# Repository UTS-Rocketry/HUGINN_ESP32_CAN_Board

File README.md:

# CAN Logger

A compact CAN bus logger and sniffer built for the Shingleback rocket. Built around the ESP32-C3 and SN65HVD230 transceiver, it sits on the CAN bus during ground support and pre-launch operations, streaming frames from the flight computer, sensor nodes, CAS board, and camera board over WiFi via MQTT for real-time monitoring.

## Overview

This board is designed for ground support and pre-launch monitoring of the Shingleback CAN bus. It passively sniffs CAN traffic and publishes decoded frames to an MQTT broker over WiFi, making it easy to verify system state, check sensor health, and monitor inter-board communication before launch.

## Hardware

| Component | Part |
|---|---|
| Microcontroller | ESP32-C3 |
| CAN Transceiver | SN65HVD230 |
| Power Input | 3.3V |

## Features

- CAN 2.0A/B frame capture
- Real-time publishing over WiFi via MQTT
- Passive monitoring, no interference with the CAN bus
- Compact form factor suitable for ground support equipment

## Monitored Systems

This board is intended to sniff traffic from the following Shingleback subsystems:

- Flight computer
- CAS board
- Camera board

## Status

Early prototype / bring-up phase. Not recommended for production use.

## License

MIT

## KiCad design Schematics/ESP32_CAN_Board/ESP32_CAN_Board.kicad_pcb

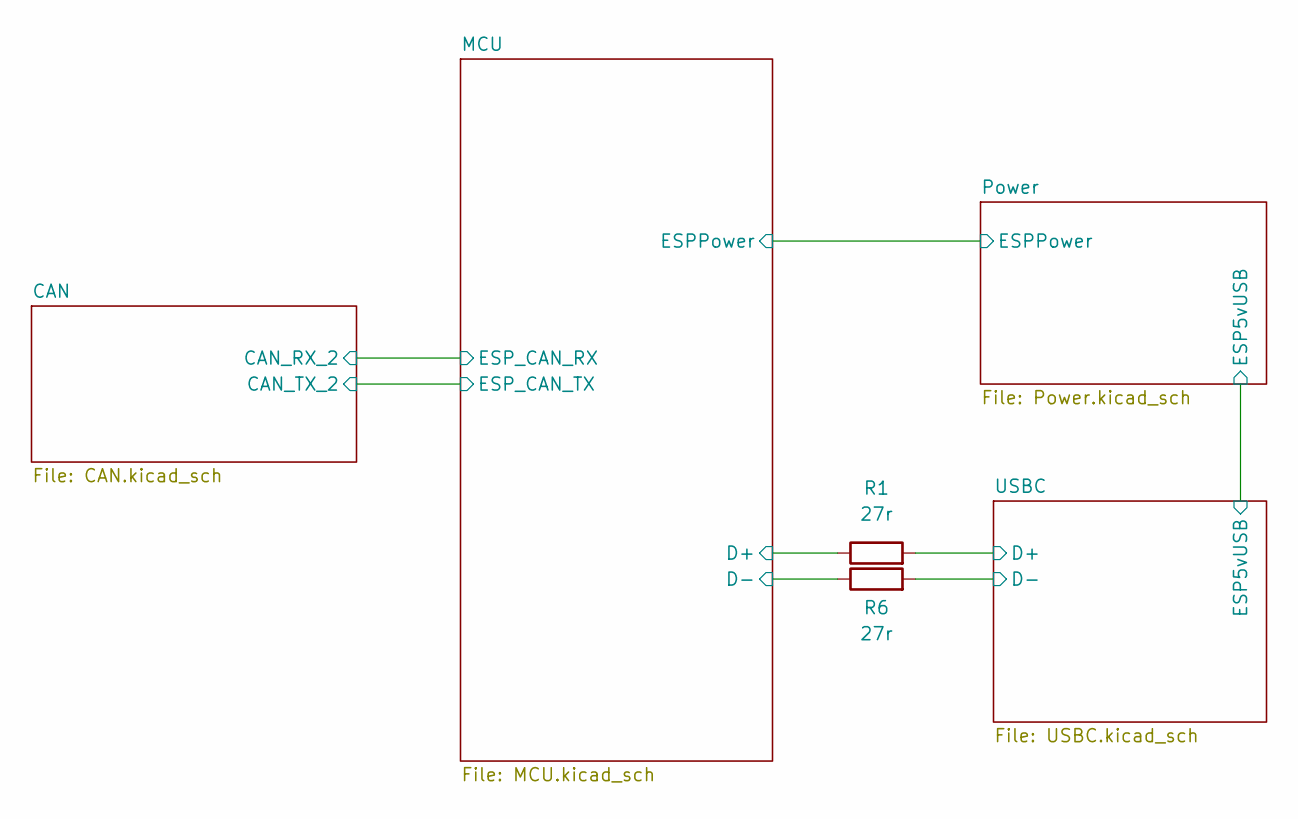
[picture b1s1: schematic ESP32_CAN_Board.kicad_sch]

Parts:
R1, R6: 27r; R_0805_2012Metric_Pad1.20x1.40mm_HandSolder; LCSC C17594

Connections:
/MCU/D+: R1.1; also elsewhere on the board
/MCU/D-: R6.1; also elsewhere on the board
/USBC/D+: R1.2; also elsewhere on the board
/USBC/D-: R6.2; also elsewhere on the board

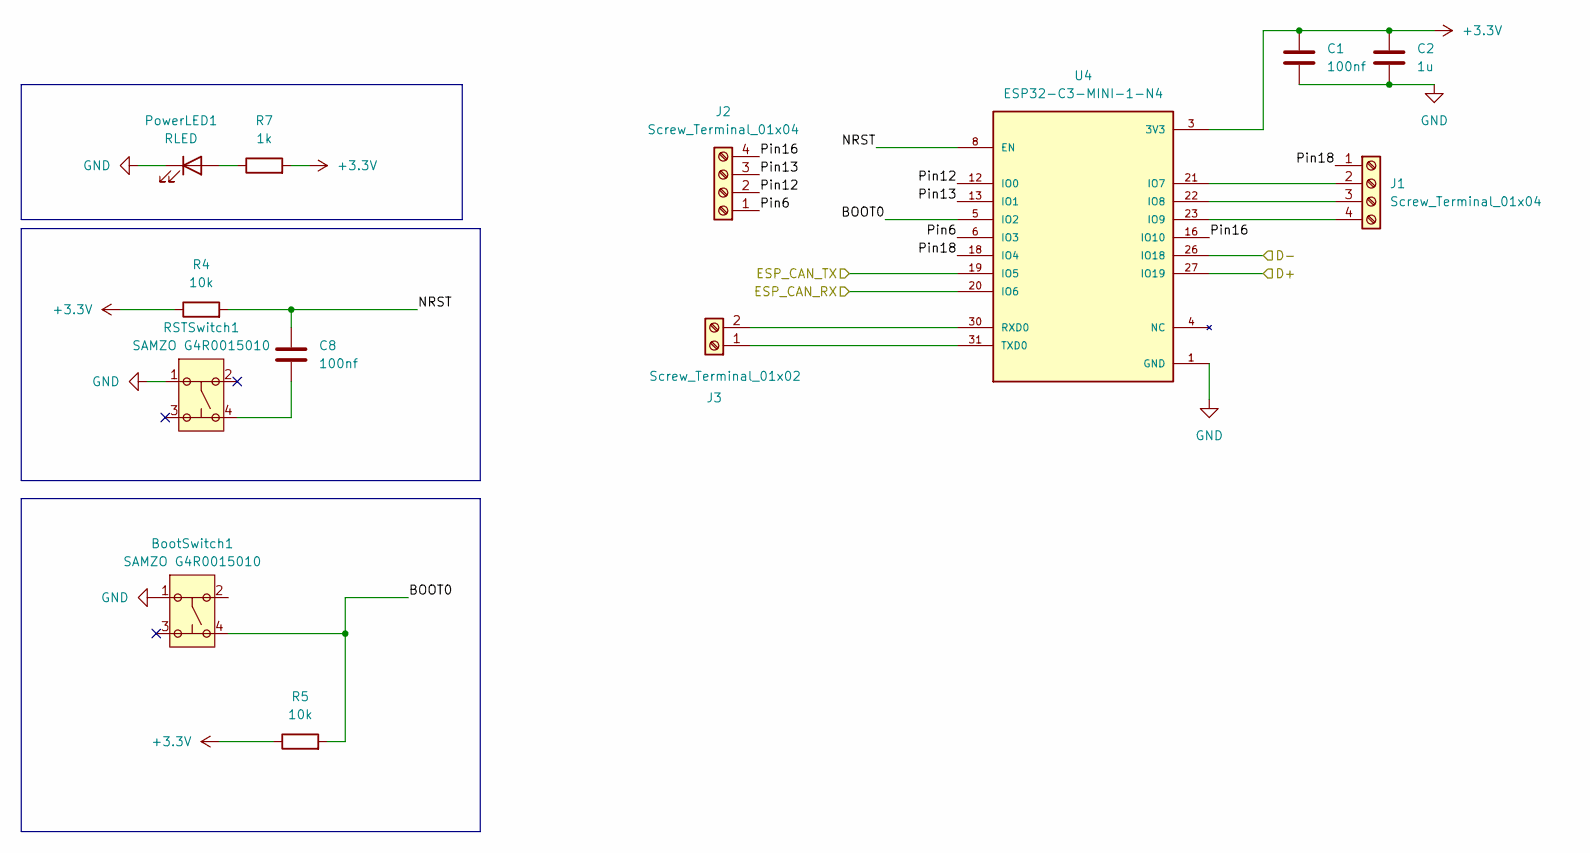
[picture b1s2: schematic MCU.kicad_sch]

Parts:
BootSwitch1: SAMZO G4R0015010; LCSC Part C49393646
C1: 100nf; C_0805_2012Metric_Pad1.18x1.45mm_HandSolder; LCSC C49678
C2: 1u; C_0805_2012Metric_Pad1.18x1.45mm_HandSolder; LCSC C28323
C8: 100nf; C_0805_2012Metric_Pad1.18x1.45mm_HandSolder; LCSC Part C49678
J1, J2: Screw_Terminal_01x04; TerminalBlock_Xinya_XY308-2.54-4P_1x04_P2.54mm_Horizontal; LCSC C915913
J3: Screw_Terminal_01x02; TerminalBlock_Xinya_XY308-2.54-2P_1x02_P2.54mm_Horizontal; LCSC C557685
PowerLED1: RLED; LED_0603_1608Metric_Pad1.05x0.95mm_HandSolder; LCSC C965799
R4: 10k; R_0805_2012Metric_Pad1.20x1.40mm_HandSolder; LCSC Part C84376
R5: 10k; R_0805_2012Metric_Pad1.20x1.40mm_HandSolder; LCSC Part C96346
R7: 1k; R_0805_2012Metric_Pad1.20x1.40mm_HandSolder; LCSC C17513
RSTSwitch1: SAMZO G4R0015010; LCSC Part C49393646
U4: ESP32-C3-MINI-1-N4; XCVR_ESP32-C3-MINI-1-N4; PARTREV v1.0; LCSC C2838502

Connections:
+3.3V: C1.1, C2.1, R4.1, R5.1, R7.2, U4.3 (3V3); also elsewhere on the board
/CAN/CAN_RX_2: U4.20 (IO6); also elsewhere on the board
/CAN/CAN_TX_2: U4.19 (IO5); also elsewhere on the board
/MCU/BOOT0: BootSwitch1.4, R5.2, U4.5 (IO2)
/MCU/D+: U4.27 (IO19); also elsewhere on the board
/MCU/D-: U4.26 (IO18); also elsewhere on the board
/MCU/NRST: C8.1, R4.2, U4.8 (EN)
/MCU/Pin6: J2.1, U4.6 (IO3)
/MCU/Pin12: J2.2, U4.12 (IO0)
/MCU/Pin13: J2.3, U4.13 (IO1)
/MCU/Pin16: J2.4, U4.16 (IO10)
/MCU/Pin18: J1.1, U4.18 (IO4)
GND: BootSwitch1.1, C1.2, C2.2, PowerLED1.1 (K), RSTSwitch1.1, U4.1 (GND), U4.2 (GND), U4.11 (GND), U4.14 (GND), U4.36 (GND), U4.37 (GND), U4.38 (GND), U4.39 (GND), U4.40 (GND), U4.41 (GND), U4.42 (GND), U4.43 (GND), U4.44 (GND), U4.45 (GND), U4.46 (GND), U4.47 (GND), U4.48 (GND), U4.49_1 (GND), U4.49_2 (GND), U4.49_3 (GND), U4.49_4 (GND), U4.49_5 (GND), U4.49_6 (GND), U4.49_7 (GND), U4.49_8 (GND), U4.49_9 (GND), U4.50 (GND), U4.51 (GND), U4.52 (GND), U4.53 (GND); also elsewhere on the board
unnamed: C8.2, RSTSwitch1.4
unnamed: J1.2, U4.21 (IO7)
unnamed: J1.3, U4.22 (IO8)
unnamed: J1.4, U4.23 (IO9)
unnamed: J3.1, U4.31 (TXD0)
unnamed: J3.2, U4.30 (RXD0)
unnamed: PowerLED1.2 (A), R7.1

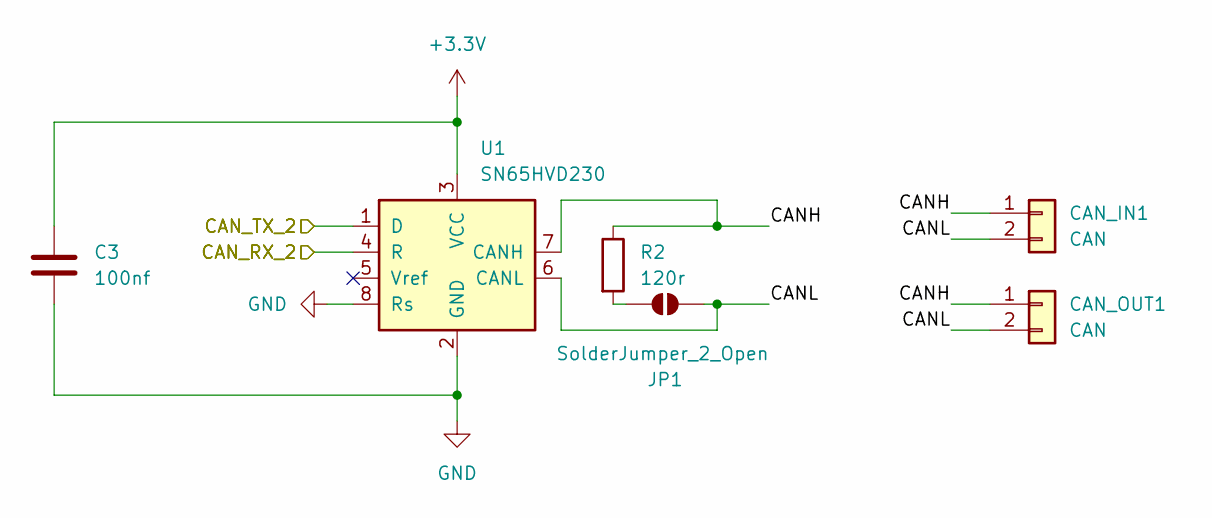
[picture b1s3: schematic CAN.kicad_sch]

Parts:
C3: 100nf; C_0805_2012Metric_Pad1.18x1.45mm_HandSolder; LCSC Part C49678
CAN_IN1: CAN; MOLEX_26013114; LCSC Part C17644051
CAN_OUT1: CAN; MOLEX_26013114; LCSC Part C17644051
JP1: SolderJumper_2_Open; SolderJumper-2_P1.3mm_Open_TrianglePad1.0x1.5mm
R2: 120r; R_0805_2012Metric_Pad1.20x1.40mm_HandSolder; LCSC Part C269726
U1: SN65HVD230; SOIC-8_3.9x4.9mm_P1.27mm; LCSC Part C1543812

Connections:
+3.3V: C3.1, U1.3 (VCC); also elsewhere on the board
/CAN/CANH: CAN_IN1.1, CAN_OUT1.1, R2.1, U1.7 (CANH)
/CAN/CANL: CAN_IN1.2, CAN_OUT1.2, JP1.2 (B), U1.6 (CANL)
/CAN/CAN_RX_2: U1.4 (R); also elsewhere on the board
/CAN/CAN_TX_2: U1.1 (D); also elsewhere on the board
GND: C3.2, U1.2 (GND), U1.8 (Rs); also elsewhere on the board
unnamed: JP1.1 (A), R2.2

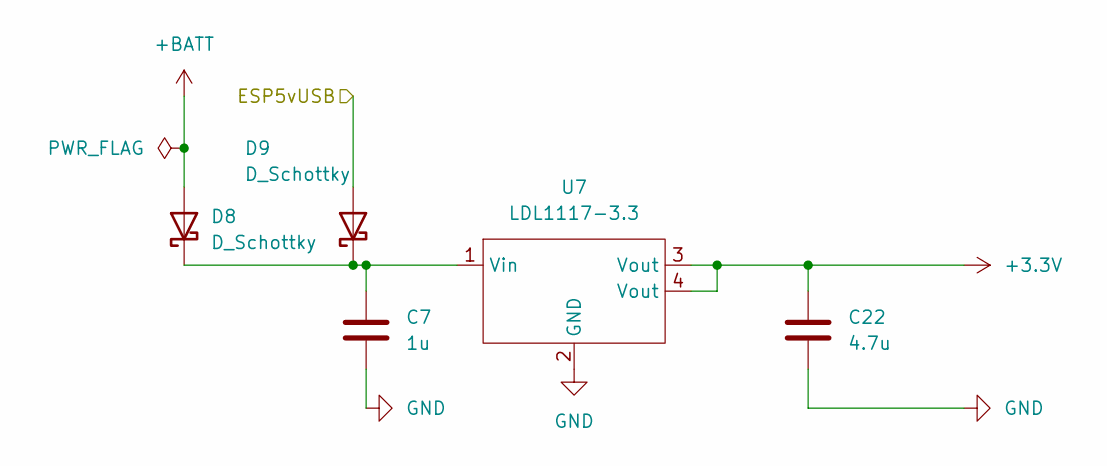
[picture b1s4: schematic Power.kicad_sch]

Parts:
C7: 1u; C_0805_2012Metric_Pad1.18x1.45mm_HandSolder; LCSC Part C28323
C22: 4.7u; C_0805_2012Metric_Pad1.18x1.45mm_HandSolder; LCSC Part C98192
D8, D9: D_Schottky; D_2114_3652Metric; LCSC C113936
U7: LDL1117-3.3; SOT230P700X180-4N; LCSC C435835

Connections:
+3.3V: C22.1, U7.3 (Vout), U7.4 (Vout); also elsewhere on the board
+BATT: D8.2 (A); also elsewhere on the board
/USBC/ESP5vUSB: D9.2 (A); also elsewhere on the board
GND: C7.2, C22.2, U7.2 (GND); also elsewhere on the board
unnamed: C7.1, D8.1 (K), D9.1 (K), U7.1 (Vin)

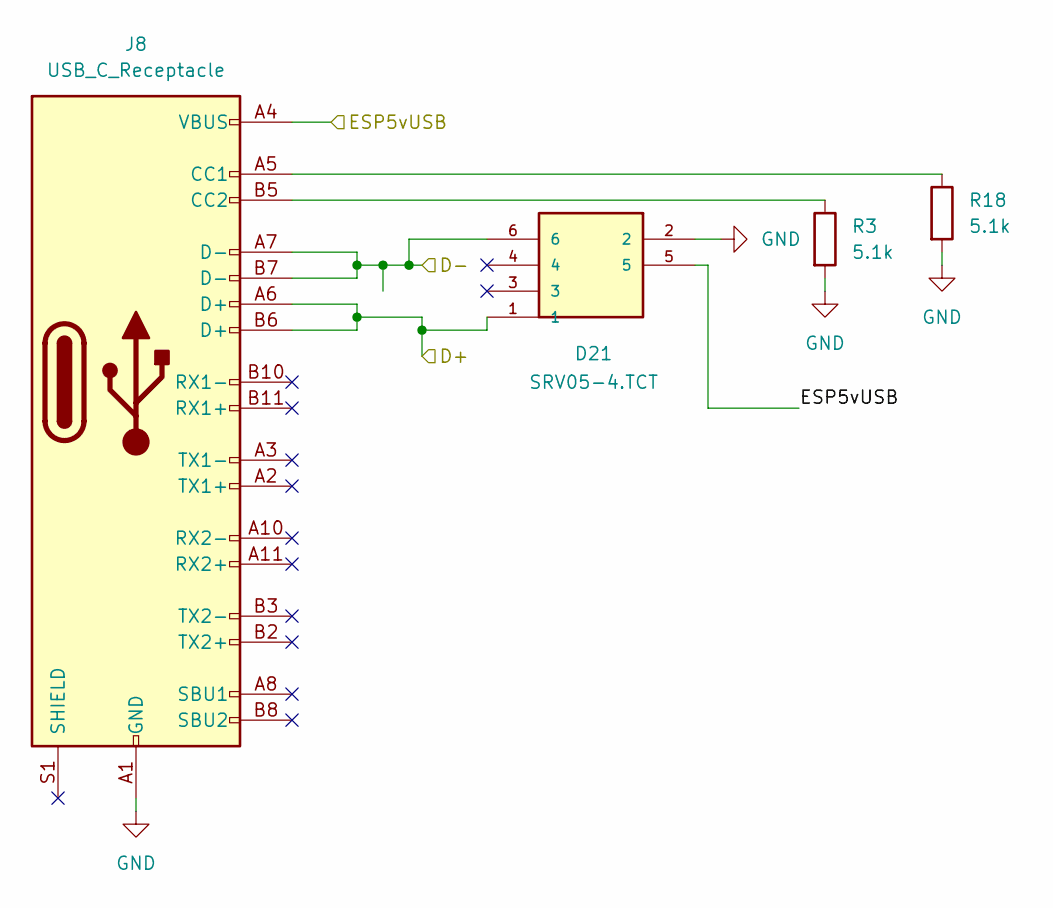
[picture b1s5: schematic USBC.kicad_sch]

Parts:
D21: SRV05-4.TCT; SOT95P280X145-6N; MOUSER_PART_NUMBER 947-SRV05-4.TCT
J8: USB_C_Receptacle; USB_C_Receptacle_HRO_TYPE-C-31-M-12; LCSC C165948
R3, R18: 5.1k; R_0805_2012Metric_Pad1.20x1.40mm_HandSolder; LCSC C27834

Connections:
/USBC/D+: D21.1, J8.A6 (D+), J8.B6 (D+); also elsewhere on the board
/USBC/D-: D21.6, J8.A7 (D-), J8.B7 (D-); also elsewhere on the board
/USBC/ESP5vUSB: D21.5, J8.A4 (VBUS), J8.A9 (VBUS), J8.B4 (VBUS), J8.B9 (VBUS); also elsewhere on the board
GND: D21.2, J8.A1 (GND), J8.A12 (GND), J8.B1 (GND), J8.B12 (GND), R3.2, R18.2; also elsewhere on the board
unnamed: J8.A5 (CC1), R18.1
unnamed: J8.B5 (CC2), R3.1

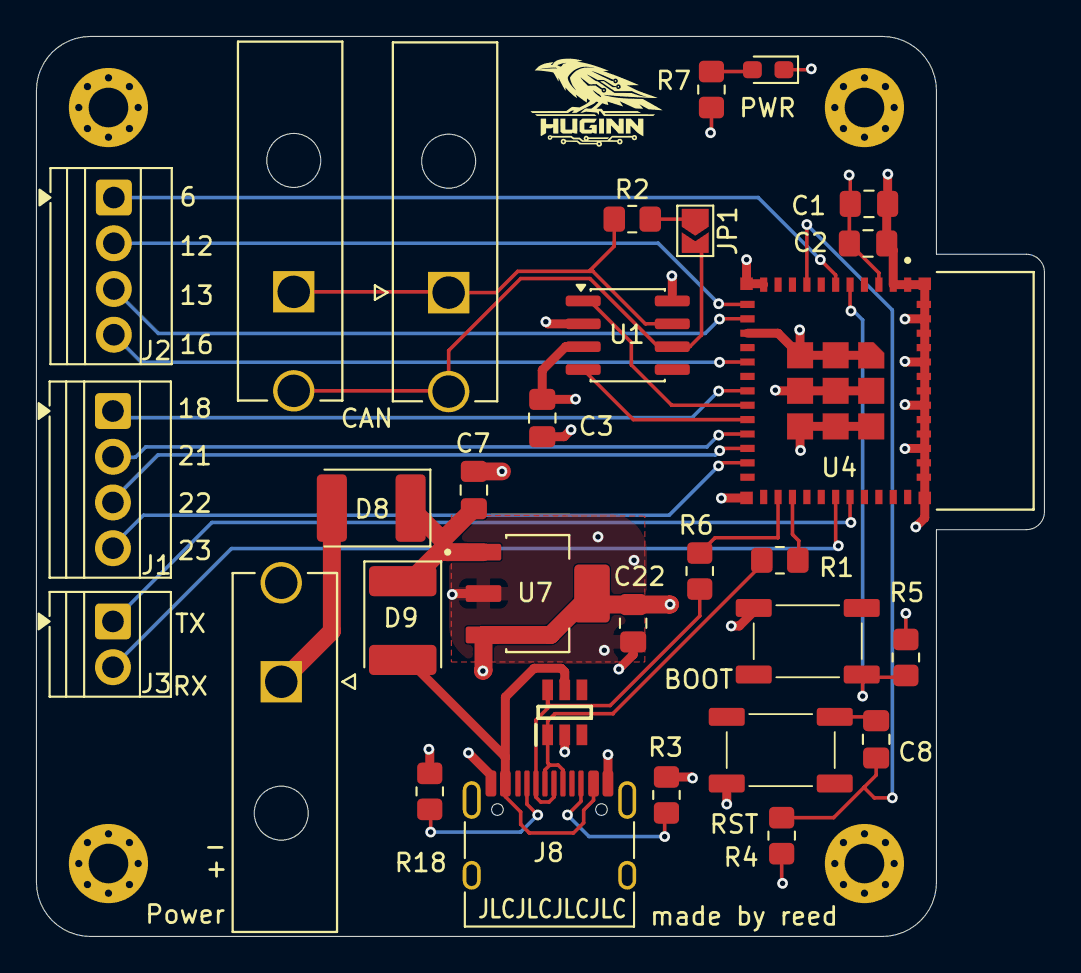
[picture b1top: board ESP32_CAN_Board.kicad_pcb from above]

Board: 4 copper layers, 56.0 x 50.0 mm, 31 parts (0 on the bottom side), 30 nets.

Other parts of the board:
PowerIn1: 2 pin Molex; MOLEX_26013114

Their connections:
+BATT: PowerIn1.1; also elsewhere on the board
GND: PowerIn1.2; also elsewhere on the board

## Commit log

2026-03-27 initial design completed
2026-03-27 finished ready for order
2026-03-27 mcu schematic update
2026-03-30 final Draft Completed, In JLPCB Cart
2026-03-31 updated ESPBoard
